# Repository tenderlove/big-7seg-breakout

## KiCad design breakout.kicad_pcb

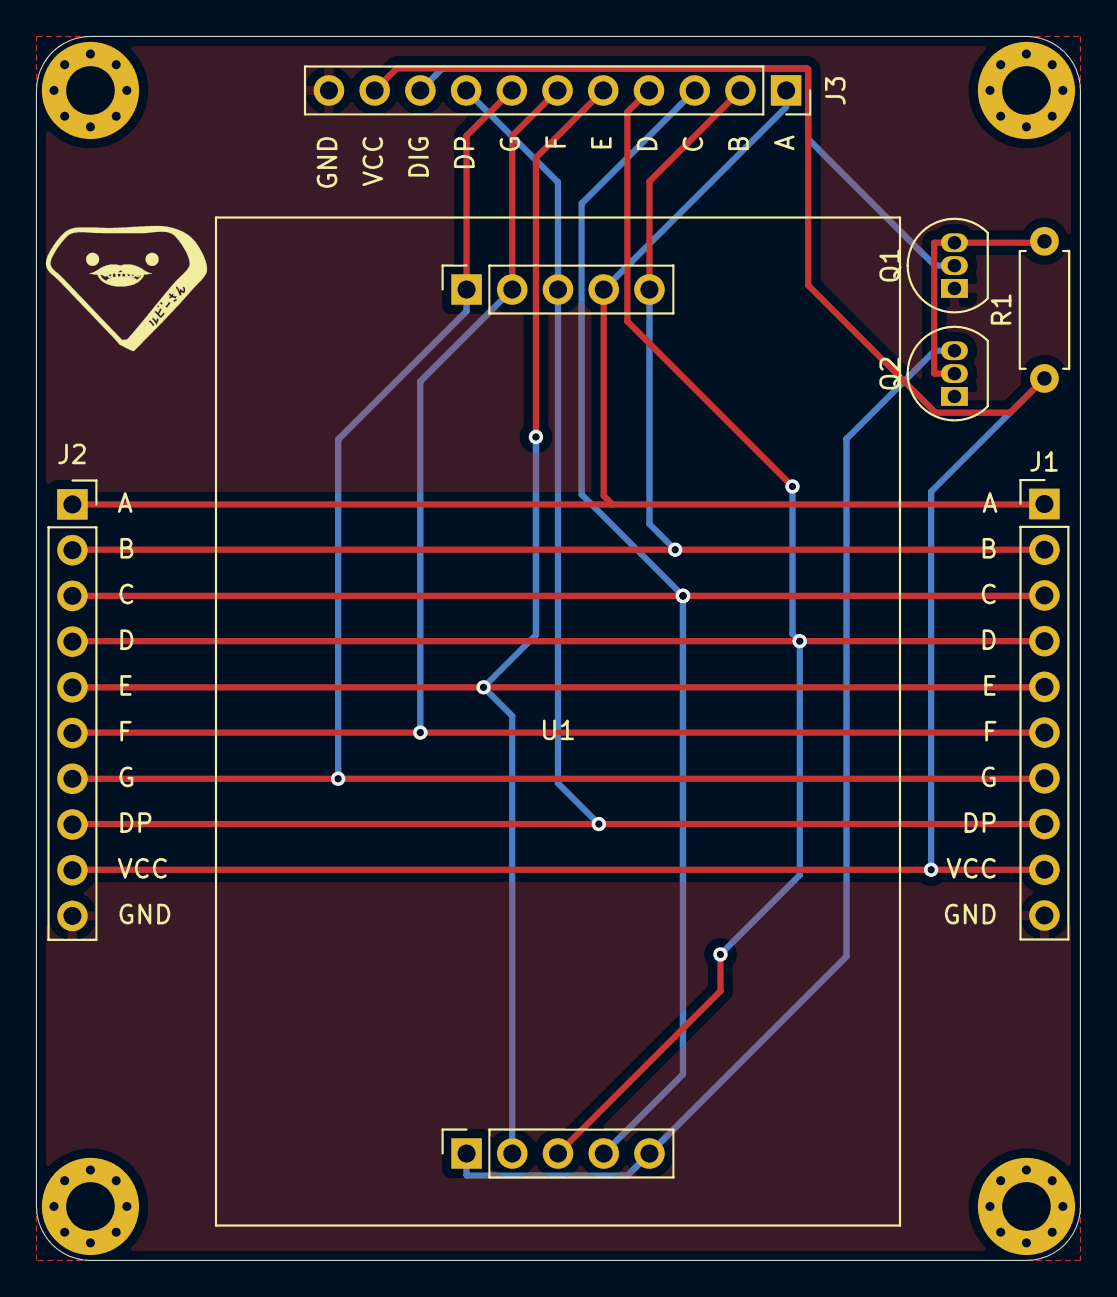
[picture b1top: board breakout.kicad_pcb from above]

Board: 2 copper layers, 58.0 x 68.0 mm, 7 parts (0 on the bottom side), 13 nets.

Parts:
J1: Right Side Male; PinHeader_1x10_P2.54mm_Vertical
J2: Left Side Female; PinSocket_1x10_P2.54mm_Vertical
J3: Header Connector; PinSocket_1x11_P2.54mm_Vertical
Q1, Q2: 2N7000; TO-92_Inline
R1: R; R_Axial_DIN0207_L6.3mm_D2.5mm_P7.62mm_Horizontal
U1: SH18101AS; SH1801AS

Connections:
/A: J1.1, J2.1, J3.1, U1.10
/B: J1.2, J2.2, J3.2, U1.9
/C: J1.3, J2.3, J3.3, U1.8
/D: J1.4, J2.4, J3.4, U1.5
/DP: J1.8, J2.8, J3.8, U1.7
/E: J1.5, J2.5, J3.5, U1.4
/F: J1.6, J2.6, J3.6, U1.2
/G: J1.7, J2.7, J3.7, U1.3
DIG: J3.9, Q1.2
GND: J1.10, J2.10, J3.11, Q1.1, Q2.1
unnamed: Q1.3, Q2.2, R1.2
unnamed: Q2.3, U1.1, U1.6
VCC: J1.9, J2.9, J3.10, R1.1

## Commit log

2020-07-28 initial
2020-07-28 second
2020-07-28 adding case
